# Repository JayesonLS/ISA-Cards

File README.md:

ISA-Cards
=========

ISA card designs for use in Vintage PCs.

ISA Template
============

**Status:** Fit tested and appears correct.

**Description:** A template from which to build ISA cards. The board dimensions
around the edge connector are from an early IBM PC Technical
Reference Manual (5150 or 5160). The rear bracket positioning
has been measured from an original IBM floppy controller taken
from an IBM 5150. This board was an excellent fit when test-fitted
in an early Tandy 1000 (25-1000).

The mounting for the CF adapter has also been comfirmed in the
same Tandy 1000. It too was a excellent fit. 

There may be some variation in fit due to various tolerances. 
The fit does not seem to be particularly important - a wide variation
in fit has been found across various commercial ISA cards.

Tandy PLUS Template
===================

**Status:** Untested.

**Description:** A template from which to design cards and/or back plates
for the Tandy 1000 EX/HX computers. Includes approximate board outlines
as measured from Tandy's memory/DMA board, Tandy's serial board and
Rob Krinecki's 3 in 1 board. Includes various notes about safe areas,
potential places to extend the board dimensions, etc.

CF-Combo-Super-Lite <sup>1, 2</sup>
===================

**Status:** Design built and tested in all configurations. **There is a currently
an error which may cause issues when other devices are performing DMA transfers.
Recommend only the Tandy 1000 configuration of this card which has no DMA present.** 
 
**Description:** An 8 bit ISA card with fully-contained compact flash card and
XT-IDE BIOS. This simplified design uses only 3 ICs for the CF/BIOS functionality.
It makes use of a commonly availalbe, inexpensive compact flash adapter with
integrated mounting bracket.

The board optionally supports the following features:

* An integrated DS1216-E compatible SmartWatch. See 
  https://github.com/JayesonLS/SmartWatchRedux for more information
   about the Dallas SmartWatch.
* 512K of SRAM for the Tandy 1000, 1000A or 1000 HD models only
  (25-1000, 25-1000A, 25-1001). This will bring a stock Tandy
  1000 to 640K. Remove any other memory upgradebefore installing.
  *Do not use the 512K RAM option in any other model of Tandy 1000
  or PC. The memory mapping is only correct for the supported Tandy
  1000 models and will result in memory conflicts in any other system.*

BasicSerial
===========

**Status:** Built and fully tested. The Rear bracket is located too
high and needs to be corrected. No other issues found.

**Description:** Adds a single 9 pin serial port to a vintage PC. Created with early
Tandy 1000's in mind which have no COM ports from the factory.

Decoding is handled by a 74xx688. Alternatively, a JED file is provided
for programming the needed decode functionality into a GAL16V8/ATF16V8.

**Configuration:** Before installing, configure the port selection jumpers
to a COM port not yet present in the system. Details are located on the
board by the port jumpers. Configure the IRQ jumper to an approriate
selection. For no IRQ, remove the IRQ jumper. Suggested IRQ settings are
located on the board by the IRQ jumper.

DualSerial <sup>1</sup>
==========

**Status:** Untested. Vertical positions of serial connectors are only
approximate (waiting on a bracket to arrive for reference).

**Description:** Adds *two* 9 pin serial ports to a vintage PC. Created with early
Tandy 1000's in mind which have no COM ports from the factory.

**Configuration:** Before installing, configure the port selection jumpers
to COM ports not yet present in the system. Details are located on the
board by the port jumpers. Configure the IRQ jumpers to an approriate
selection. For no IRQ, remove the IRQ jumper. Suggested IRQ settings are
located on the board by the IRQ jumpers.

EX-HX Combo <sup>1, 2</sup>
===========

**Status:** Still in design.

**Description:** Multiple upgrades for the Tandy 1000 EX/HX
in a single board. It adds the following:
* Up to 384K of additional base memory to bring the EX/HX up
  to 640K
* Up to 160K of upper memory (UMB)
* Rear accessable CF card slot
* XT-IDE BIOS
* Serial port with 16550 UART 
* DS1316 SmartWatch real time clock

Functionality is very similar to Rob Krinecki's 3 in 1/4 in 1 boards,
with the following differences:
* Can be fitted in either the lower or middle board position on the
  EX/HX.
* Can be used together with Tandy's original DMA/memory board. This
  configuration adds DMA functionality and makes the top board 
  position available for a third upgrade board.
* Support for additional upper memory on the Tandy 1000 EX. The EX
  allows for more upper memory than the HX due to the EX having a
  smaller system ROM than the HX. 
* Base and upper memory configuration, COM port selection, COM IRQ,
  ATA (IDE) port address, etc. are configurable via dip switches.
  Using the default settings, the board is equivalent to the proven
  configuration of Rob Krineki's 3 in 1 board.

Riser
=====

**Status:** Tested and works well. 

**Description:** Raises an 8 bit ISA card up out of a desktop case. Makes it easier
to probe ISA cards during development/testing. Can optionally fuse
the ISA power rails. Low-ohm resistors can be fitted to the power 
rails to assist with current measurement. ISA pins are marked for 
easy identification.

Not intended for permanent installation. 

The bracket is from a Compact Flash to IDE adapter intended for
installation into PCI slots. It must be raised off the board using
standoffs totalling 14.6mm high.

ISAtoTandyPlus
==============

**Status:** Untested.

**Description:** Allows connection of a Tandy 1000 EX/HX Plus board in a standard
ISA slot. Intended for use on an ISA riser board for 
development/testing. 

Not intended for permanent installation.

---------------
<sup>**1**</sup> Construction requires programming of one or
    more GAL16V8/ATF16V8 and/or GAL22V10/ATF22V10 simple programmable
    logic devices. JED file provided. A TL866 or similar programmer
    can program most of these devices.
    
<sup>**2**</sup> Construction requires programming of the required
    BIOS image into the flash ROM. Most common programmers, such as
    the TL866, can be used for this.

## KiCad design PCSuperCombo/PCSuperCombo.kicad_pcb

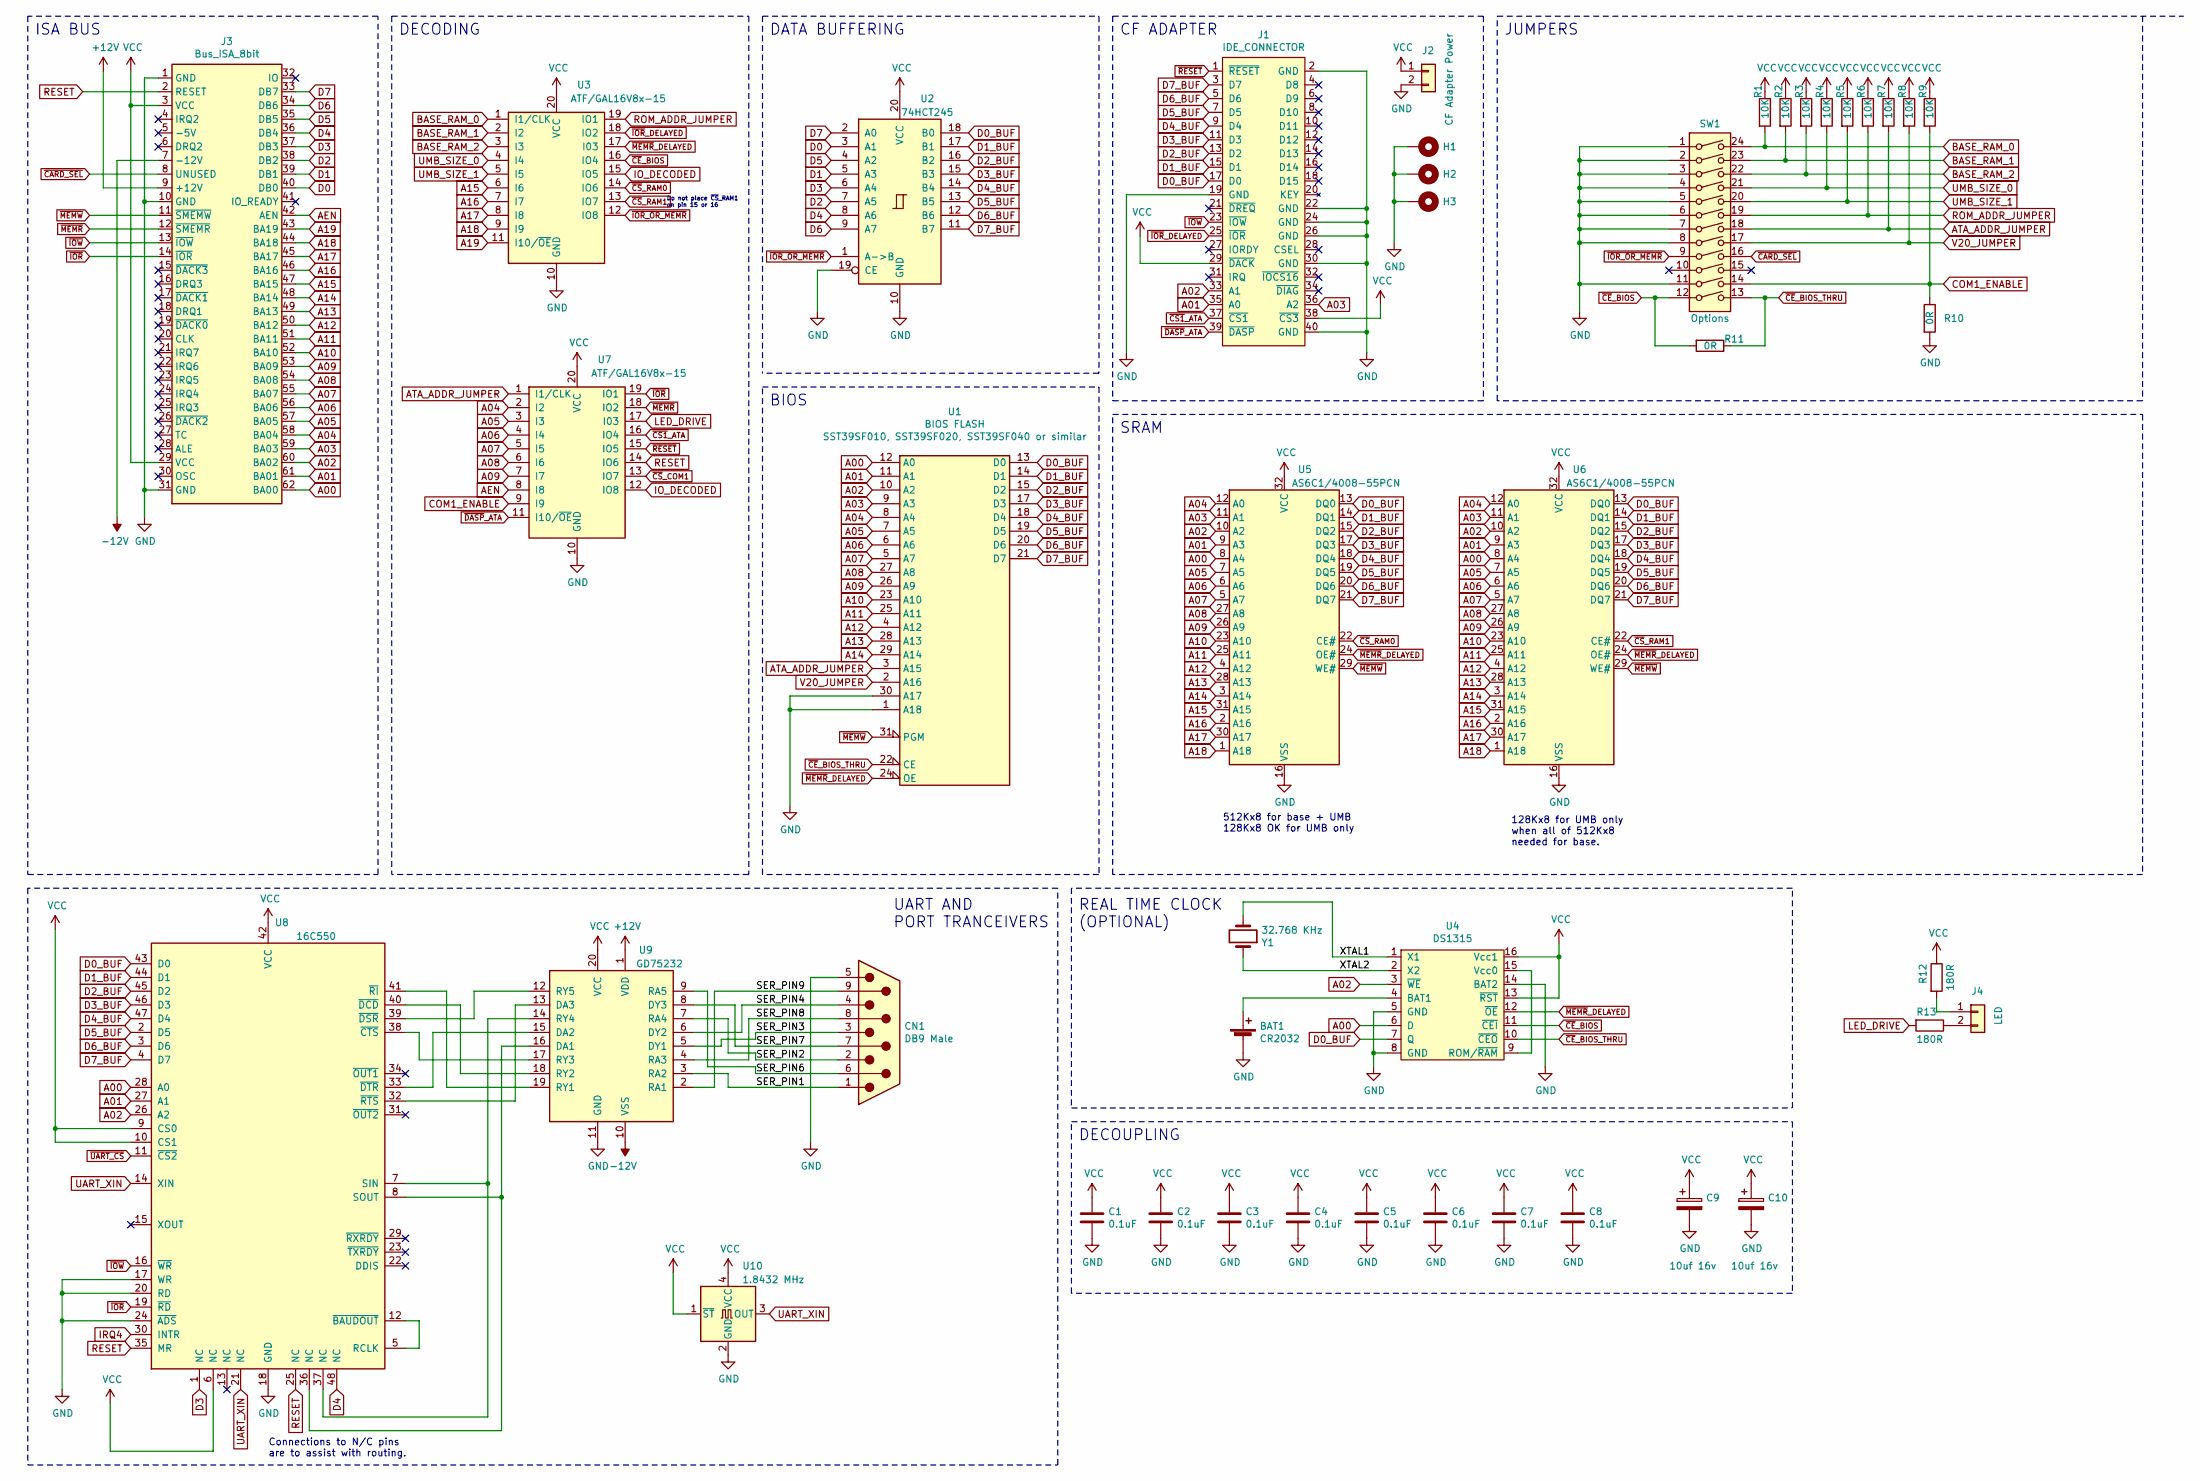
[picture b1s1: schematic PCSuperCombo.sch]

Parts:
BAT1: CR2032; BatteryHolder_Keystone_103_1x20mm
C1, C2, C3, C4, C5, C6, C7, C8: 0.1uF; C_1206_3216Metric; LCSC C24497
C9, C10: 10uf 16v; CP_EIA-3216-18_Kemet-A; LCSC C7171
CN1: DB9 Male; DSUB-9_Male_Horizontal_P2.77x2.84mm_EdgePinOffset7.70mm_Hou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
H1, H2, H3: MountingHole_Pad; MountingHole_3.5mm_Pad
J1: IDE_CONNECTOR; PinSocket_2x20_P2.54mm_Vertical
J2: CF Adapter Power; PinSocket_1x02_P2.54mm_Vertical
J3: Bus_ISA_8bit; BUS_XT
J4: LED; PinHeader_1x02_P2.54mm_Horizontal
R1, R2, R3, R4, R5, R6, R7, R8, R9: 10K; R_1206_3216Metric; LCSC C17902
R10, R11: 0R; R_1206_3216Metric; LCSC C17902
R12, R13: 180R; R_1206_3216Metric; LCSC C17924
SW1: Options; SW_DIP_SPSTx12
U1: BIOS FLASH; DIP-32_W15.24mm_Socket
U2: 74HCT245; DIP-20_W7.62mm_Socket
U3, U7: ATF/GAL16V8x-15; DIP-20_W7.62mm_Socket
U4: DS1315; DIP-16_W7.62mm_Socket
U5, U6: AS6C1/4008-55PCN; DIP-32_W15.24mm_Socket
U8: 16C550; LQFP-48_7x7mm_P0.5mm; Part options C181382, C2692304, C84320, C352984; LCSC C181382
U9: GD75232; SOIC-20W_7.5x12.8mm_P1.27mm; LCSC C6662
U10: 1.8432 MHz; Oscillator_SMD_SeikoEpson_SG8002CA-4Pin_7.0x5.0mm; LCSC C386895
Y1: 32.768 KHz; Crystal_C38-LF_D3.0mm_L8.0mm_Horizontal

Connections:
+12V: J3.9 (+12V), U9.1 (VDD)
-12V: J3.7 (-12V), U9.10 (VSS)
/SER_PIN1: CN1.1, U9.3 (RA2)
/SER_PIN2: CN1.2, U9.7 (RA4)
/SER_PIN3: CN1.3, U9.5 (DY1)
/SER_PIN4: CN1.4, U9.6 (DY2)
/SER_PIN6: CN1.6, U9.9 (RA5)
/SER_PIN7: CN1.7, U9.8 (DY3)
/SER_PIN8: CN1.8, U9.4 (RA3)
/SER_PIN9: CN1.9, U9.2 (RA1)
/XTAL1: U4.1 (X1), Y1.2
/XTAL2: U4.2 (X2), Y1.1
A00: J3.62 (BA00), U1.12 (A0), U4.6 (D), U5.8 (A4), U6.8 (A4), U8.28 (A0)
A01: J1.35 (A0), J3.61 (BA01), U1.11 (A1), U5.9 (A3), U6.9 (A3), U8.27 (A1)
A02: J1.33 (A1), J3.60 (BA02), U1.10 (A2), U4.3 (~WE), U5.10 (A2), U6.10 (A2), U8.26 (A2)
A03: J1.36 (A2), J3.59 (BA03), U1.9 (A3), U5.11 (A1), U6.11 (A1)
A04: J3.58 (BA04), U1.8 (A4), U5.12 (A0), U6.12 (A0), U7.2 (I2)
A05: J3.57 (BA05), U1.7 (A5), U5.7 (A5), U6.7 (A5), U7.3 (I3)
A06: J3.56 (BA06), U1.6 (A6), U5.6 (A6), U6.6 (A6), U7.4 (I4)
A07: J3.55 (BA07), U1.5 (A7), U5.5 (A7), U6.5 (A7), U7.5 (I5)
A08: J3.54 (BA08), U1.27 (A8), U5.27 (A8), U6.27 (A8), U7.6 (I6)
A09: J3.53 (BA09), U1.26 (A9), U5.26 (A9), U6.26 (A9), U7.7 (I7)
A10: J3.52 (BA10), U1.23 (A10), U5.23 (A10), U6.23 (A10)
A11: J3.51 (BA11), U1.25 (A11), U5.25 (A11), U6.25 (A11)
A12: J3.50 (BA12), U1.4 (A12), U5.4 (A12), U6.4 (A12)
A13: J3.49 (BA13), U1.28 (A13), U5.28 (A13), U6.28 (A13)
A14: J3.48 (BA14), U1.29 (A14), U5.3 (A14), U6.3 (A14)
A15: J3.47 (BA15), U3.6 (I6), U5.31 (A15), U6.31 (A15)
A16: J3.46 (BA16), U3.7 (I7), U5.2 (A16), U6.2 (A16)
A17: J3.45 (BA17), U3.8 (I8), U5.30 (A17), U6.30 (A17)
A18: J3.44 (BA18), U3.9 (I9), U5.1 (A18), U6.1 (A18)
A19: J3.43 (BA19), U3.11 (I10/~OE~)
AEN: J3.42 (AEN), U7.8 (I8)
ATA_ADDR_JUMPER: R7.2, SW1.18, U1.3 (A15), U7.1 (I1/CLK)
BASE_RAM_0: R1.2, SW1.24, U3.1 (I1/CLK)
BASE_RAM_1: R2.2, SW1.23, U3.2 (I2)
BASE_RAM_2: R3.2, SW1.22, U3.3 (I3)
COM1_ENABLE: R9.2, R10.1, SW1.14, U7.9 (I9)
D0: J3.40 (DB0), U2.3 (A1)
D0_BUF: J1.17 (D0), U1.13 (D0), U2.18 (B0), U4.7 (Q), U5.13 (DQ0), U6.13 (DQ0), U8.43 (D0)
D1: J3.39 (DB1), U2.5 (A3)
D1_BUF: J1.15 (D1), U1.14 (D1), U2.17 (B1), U5.14 (DQ1), U6.14 (DQ1), U8.44 (D1)
D2: J3.38 (DB2), U2.7 (A5)
D2_BUF: J1.13 (D2), U1.15 (D2), U2.16 (B2), U5.15 (DQ2), U6.15 (DQ2), U8.45 (D2)
D3: J3.37 (DB3), U2.6 (A4), U8.1 (NC)
D3_BUF: J1.11 (D3), U1.17 (D3), U2.15 (B3), U5.17 (DQ3), U6.17 (DQ3), U8.46 (D3)
D4: J3.36 (DB4), U2.8 (A6), U8.48 (NC)
D4_BUF: J1.9 (D4), U1.18 (D4), U2.14 (B4), U5.18 (DQ4), U6.18 (DQ4), U8.47 (D4)
D5: J3.35 (DB5), U2.4 (A2)
D5_BUF: J1.7 (D5), U1.19 (D5), U2.13 (B5), U5.19 (DQ5), U6.19 (DQ5), U8.2 (D5)
D6: J3.34 (DB6), U2.9 (A7)
D6_BUF: J1.5 (D6), U1.20 (D6), U2.12 (B6), U5.20 (DQ6), U6.20 (DQ6), U8.3 (D6)
D7: J3.33 (DB7), U2.2 (A0)
D7_BUF: J1.3 (D7), U1.21 (D7), U2.11 (B7), U5.21 (DQ7), U6.21 (DQ7), U8.4 (D7)
GND: BAT1.2 (-), C1.2, C2.2, C3.2, C4.2, C5.2, C6.2, C7.2, C8.2, C9.2, C10.2, CN1.5, H1.1, H2.1, H3.1, J1.2 (GND), J1.19 (GND), J1.22 (GND), J1.24 (GND), J1.26 (GND), J1.30 (GND), J1.40 (GND), J2.2, J3.1 (GND), J3.10 (GND), J3.31 (GND), R10.2, SW1.1, SW1.2, SW1.3, SW1.4, SW1.5, SW1.6, SW1.7, SW1.8, SW1.11, U1.1 (A18), U1.16 (GND), U1.30 (A17), U2.10 (GND), U2.19 (CE), U3.10 (GND), U4.5 (GND), U4.8 (GND), U4.14 (BAT2), U5.16 (VSS), U6.16 (VSS), U7.10 (GND), U8.17 (WR), U8.18 (GND), U8.20 (RD), U8.24 (~ADS~), U9.11 (GND), U10.2 (GND)
IO_DECODED: U3.15 (IO5), U7.12 (IO8)
IRQ4: U8.30 (INTR)
LED_DRIVE: R13.2, U7.17 (I03)
unnamed: BAT1.1 (+), U4.4 (BAT1)
unnamed: J4.1, R12.2
unnamed: J4.2, R13.1
unnamed: U4.9 (ROM/~RAM), U4.15 (Vcc0)
unnamed: U8.5 (RCLK), U8.12 (~BAUDOUT~)
unnamed: U8.32 (~RTS~), U9.13 (DA3)
unnamed: U8.33 (~DTR~), U9.15 (DA2)
unnamed: U8.8 (SOUT), U8.36 (NC), U9.16 (DA1)
unnamed: U8.7 (SIN), U8.37 (NC), U9.14 (RY4)
unnamed: U8.38 (~CTS~), U9.17 (RY3)
unnamed: U8.39 (~DSR~), U9.12 (RY5)
unnamed: U8.40 (~DCD~), U9.18 (RY2)
unnamed: U8.41 (~RI~), U9.19 (RY1)
RESET: J3.2 (RESET), U7.14 (IO6), U8.25 (NC), U8.35 (MR)
ROM_ADDR_JUMPER: R6.2, SW1.19, U3.19 (IO1)
UART_XIN: U8.14 (XIN), U8.21 (NC), U10.3 (OUT)
UMB_SIZE_0: R4.2, SW1.21, U3.4 (I4)
UMB_SIZE_1: R5.2, SW1.20, U3.5 (I5)
V20_JUMPER: R8.2, SW1.17, U1.2 (A16)
VCC: C1.1, C2.1, C3.1, C4.1, C5.1, C6.1, C7.1, C8.1, C9.1, C10.1, J1.29 (~DACK), J1.38 (~CS3), J2.1, J3.3 (VCC), J3.29 (VCC), R1.1, R2.1, R3.1, R4.1, R5.1, R6.1, R7.1, R8.1, R9.1, R12.1, U1.32 (VCC), U2.20 (VCC), U3.20 (VCC), U4.13 (~RST), U4.16 (Vcc1), U5.32 (VCC), U6.32 (VCC), U7.20 (VCC), U8.6 (NC), U8.9 (CS0), U8.10 (CS1), U8.42 (VCC), U9.20 (VCC), U10.1 (~ST), U10.4 (VCC)
~CARD_SEL: J3.8 (UNUSED), SW1.16
~CE~_BIOS: R11.2, SW1.12, U3.16 (IO4), U4.11 (~CEI)
~CE~_BIOS_THRU: R11.1, SW1.13, U1.22 (CE), U4.10 (~CEO)
~CS1~_ATA: J1.37 (~CS1), U7.16 (IO4)
~CS~_COM1: U7.13 (IO7)
~CS~_RAM0: U3.14 (IO6), U5.22 (CE#)
~CS~_RAM1: U3.13 (IO7), U6.22 (CE#)
~DASP~_ATA: J1.39 (~DASP), U7.11 (I10/~OE~)
~IOR: J3.14 (~IOR), U7.19 (IO1), U8.19 (~RD~)
~IOR_OR_MEMR: SW1.9, U2.1 (A->B), U3.12 (IO8)
~IOR~_DELAYED: J1.25 (~IOR), U3.18 (IO2)
~IOW: J1.23 (~IOW), J3.13 (~IOW), U8.16 (~WR~)
~MEMR: J3.12 (~SMEMR), U7.18 (IO2)
~MEMR~_DELAYED: U1.24 (OE), U3.17 (I03), U4.12 (~OE), U5.24 (OE#), U6.24 (OE#)
~MEMW: J3.11 (~SMEMW), U1.31 (PGM), U5.29 (WE#), U6.29 (WE#)
~RESET: J1.1 (~RESET), U7.15 (IO5)
~UART_CS: U8.11 (~CS2~)

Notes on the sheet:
ISA BUS
DECOUPLING
BIOS
JUMPERS
REAL TIME CLOCK (OPTIONAL)
SRAM
512Kx8 for base + UMB 128Kx8 OK for UMB only
128Kx8 for UMB only when all of 512Kx8 needed for base.
CF ADAPTER
DECODING
DATA BUFFERING
Do not place ~CS~_RAM1 on pin 15 or 16
UART AND PORT TRANCEIVERS
Connections to N/C pins are to assist with routing.

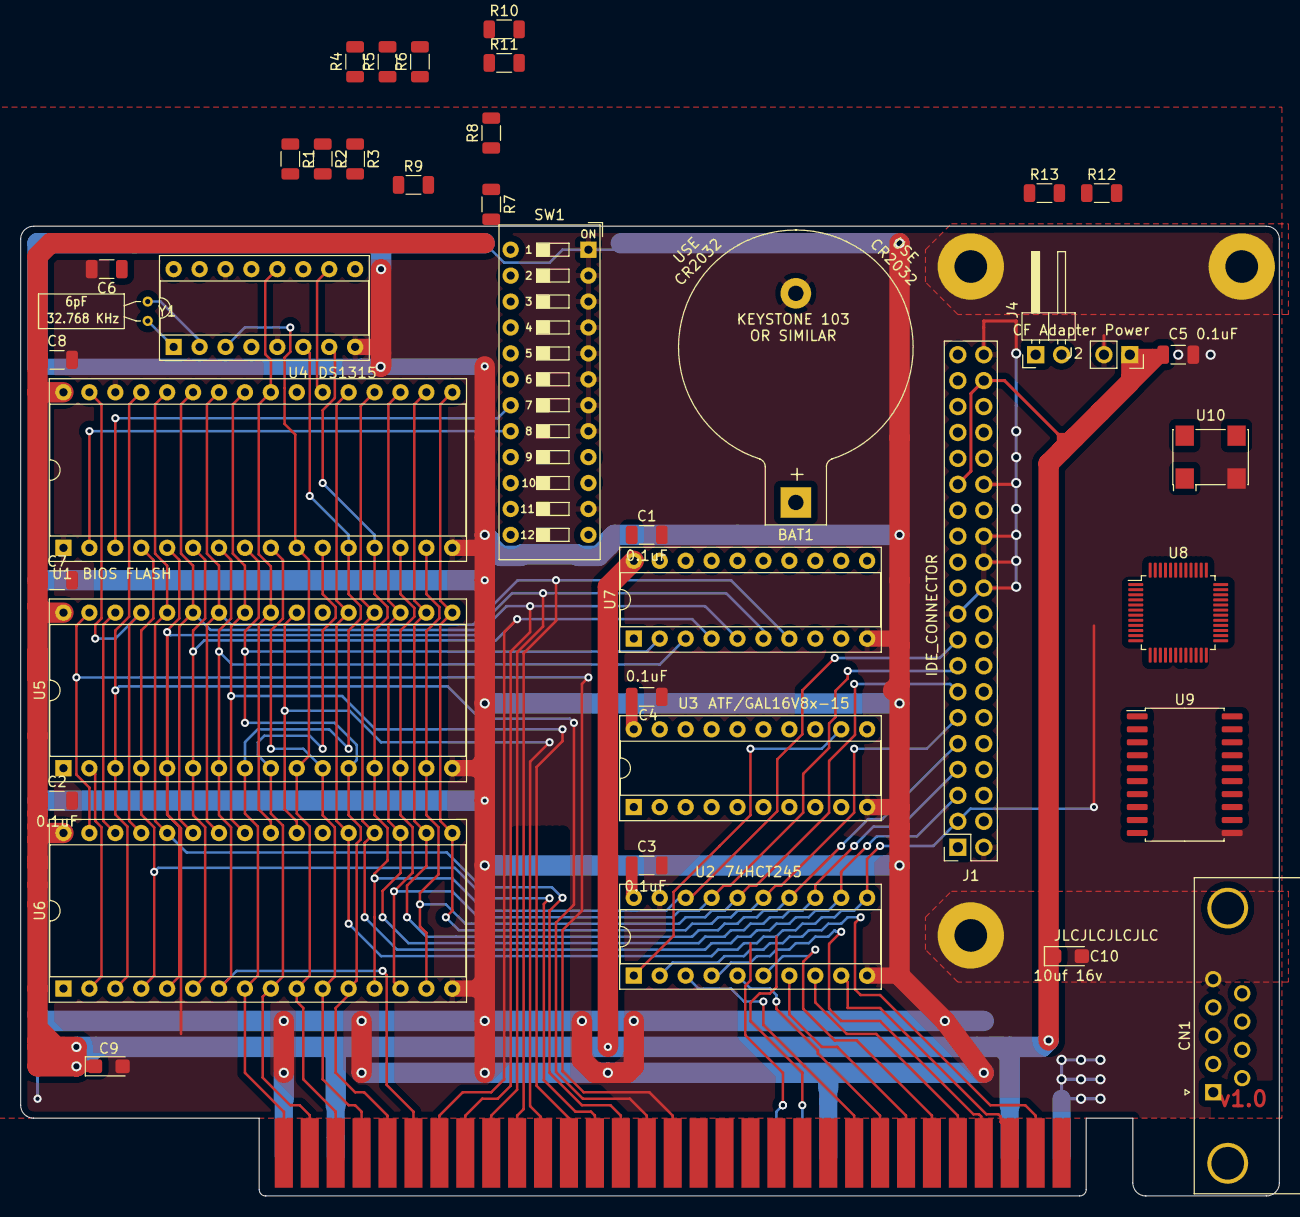
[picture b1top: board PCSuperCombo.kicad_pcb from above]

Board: 2 copper layers, 123.3 x 95.0 mm, 44 parts (0 on the bottom side), 92 nets.

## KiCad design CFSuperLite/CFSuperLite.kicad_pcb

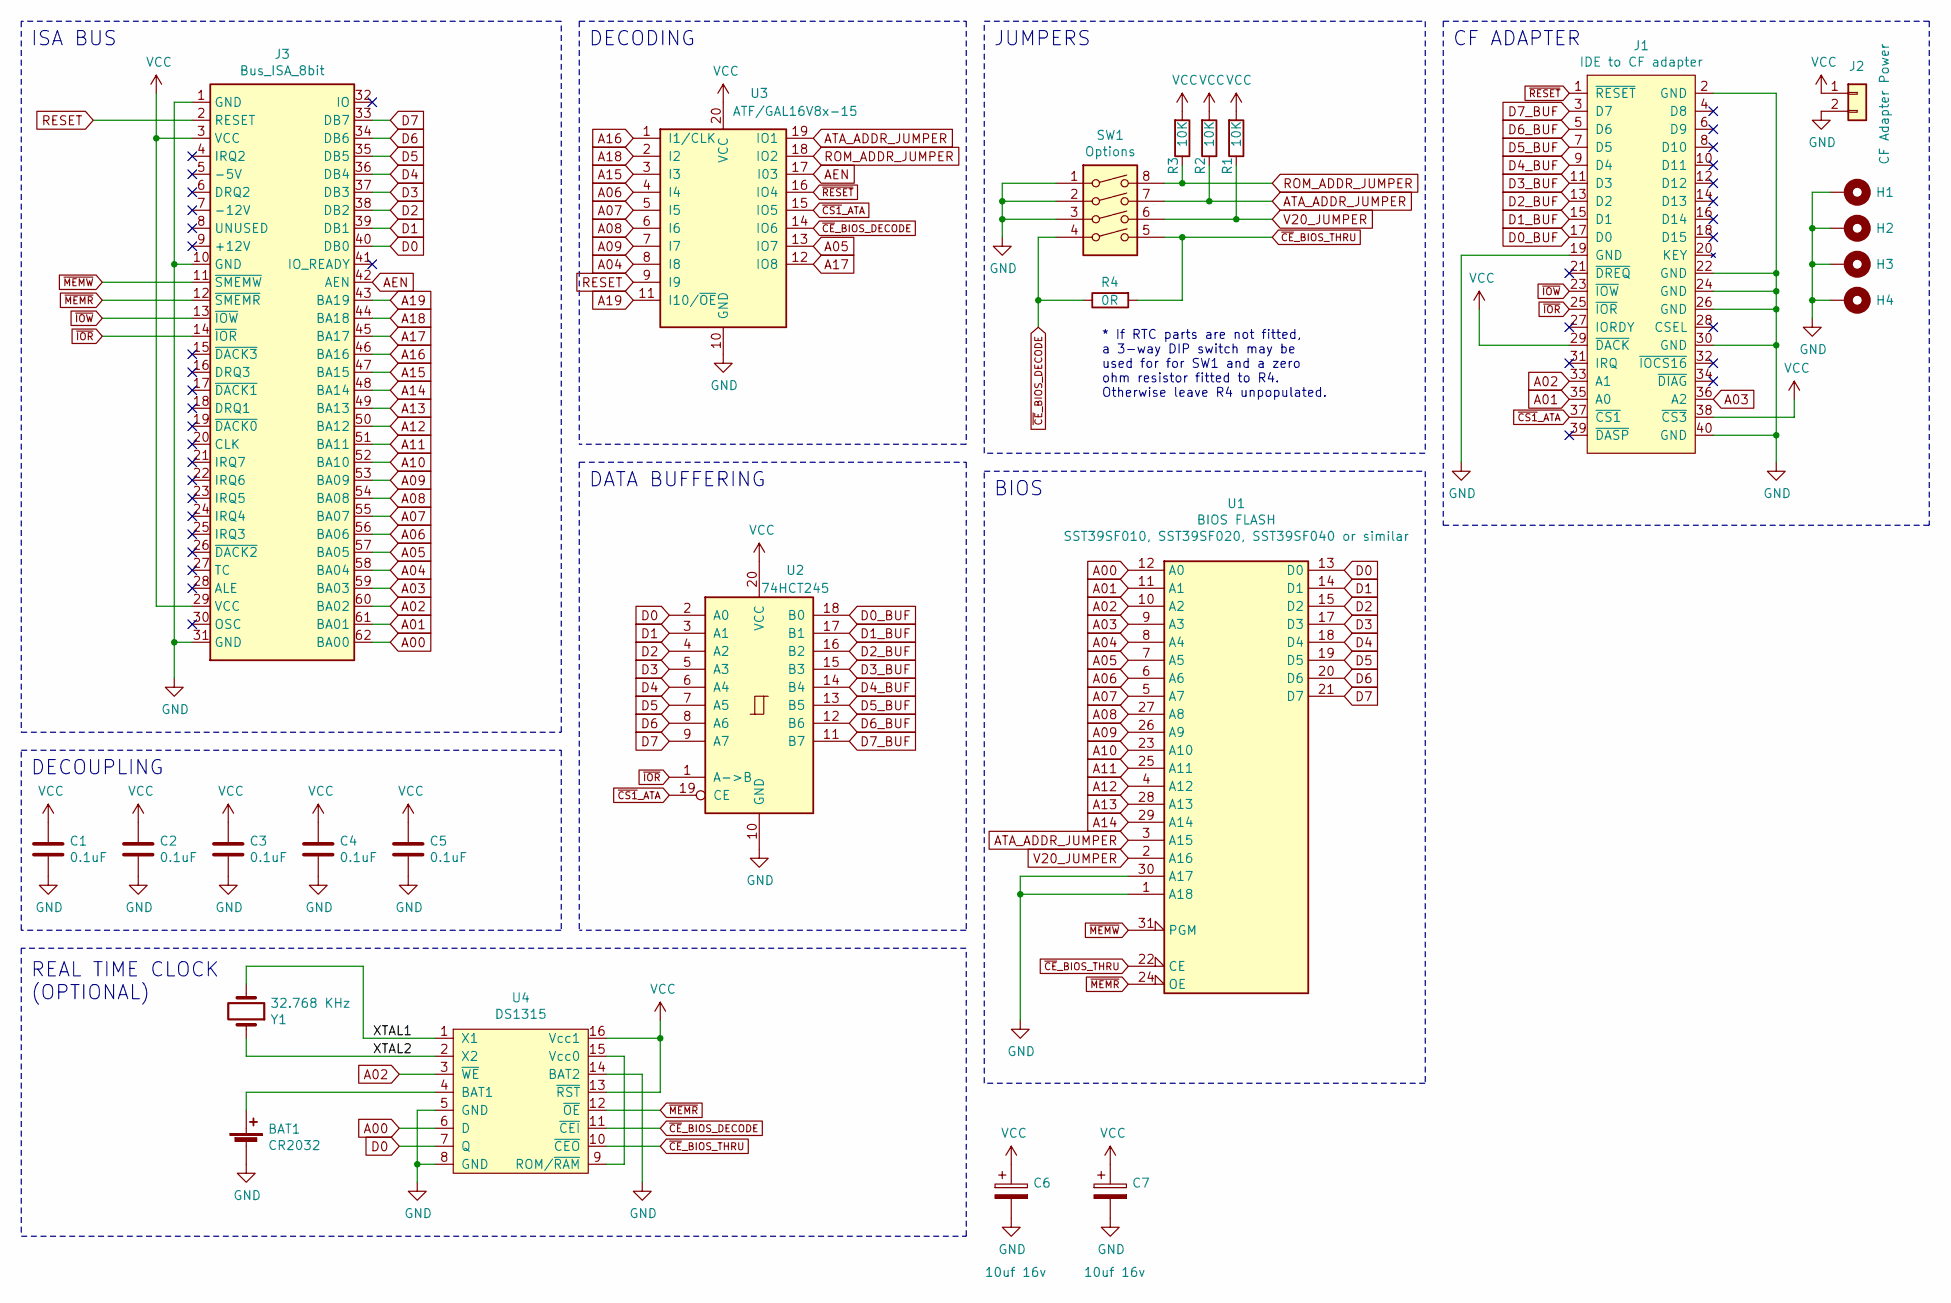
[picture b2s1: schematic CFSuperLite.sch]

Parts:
BAT1: CR2032; BatteryHolder_Keystone_103_1x20mm; Part options C964748, C964751, C964750; LCSC C964748
C1, C2, C3, C4, C5: 0.1uF; C_1206_3216Metric; LCSC C24497
C6, C7: 10uf 16v; CP_EIA-3216-18_Kemet-A; LCSC C7171
H1, H2, H3, H4: MountingHole_Pad; MountingHole_3.5mm_Pad
J1: IDE to CF adapter; PinSocket_2x20_P2.54mm_Vertical; LCSC C35165
J2: CF Adapter Power; PinSocket_1x02_P2.54mm_Vertical; Part options C225499, C49661; LCSC C225499
J3: Bus_ISA_8bit; BUS_XT
R1, R2, R3: 10K; R_1206_3216Metric; LCSC C17902
R4: 0R; R_1206_3216Metric; LCSC C17888
SW1: Options; SW_DIP_SPSTx04_Slide_9.78x12.34mm_W7.62mm_P2.54mm; Part options C15781, C99418, C319060, C47207; LCSC C15781
U1: BIOS FLASH; DIP-32_W15.24mm_Socket; Part options C72122, C146583, C2331; LCSC C146583
U2: 74HCT245; DIP-20_W7.62mm_Socket; Part options C72118, C132507, C2328; LCSC C72118
U3: ATF/GAL16V8x-15; DIP-20_W7.62mm_Socket; Part options C72118, C132507, C2328; LCSC C72118
U4: DS1315; DIP-16_W7.62mm_Socket; Part options C72115, C146580, C2326; LCSC C72115
Y1: 32.768 KHz; Crystal_C38-LF_D3.0mm_L8.0mm_Horizontal; LCSC C127496

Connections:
/XTAL1: U4.1 (X1), Y1.2
/XTAL2: U4.2 (X2), Y1.1
A00: J3.62 (BA00), U1.12 (A0), U4.6 (D)
A01: J1.35 (A0), J3.61 (BA01), U1.11 (A1)
A02: J1.33 (A1), J3.60 (BA02), U1.10 (A2), U4.3 (~WE)
A03: J1.36 (A2), J3.59 (BA03), U1.9 (A3)
A04: J3.58 (BA04), U1.8 (A4), U3.8 (I8)
A05: J3.57 (BA05), U1.7 (A5), U3.13 (IO7)
A06: J3.56 (BA06), U1.6 (A6), U3.4 (I4)
A07: J3.55 (BA07), U1.5 (A7), U3.5 (I5)
A08: J3.54 (BA08), U1.27 (A8), U3.6 (I6)
A09: J3.53 (BA09), U1.26 (A9), U3.7 (I7)
A10: J3.52 (BA10), U1.23 (A10)
A11: J3.51 (BA11), U1.25 (A11)
A12: J3.50 (BA12), U1.4 (A12)
A13: J3.49 (BA13), U1.28 (A13)
A14: J3.48 (BA14), U1.29 (A14)
A15: J3.47 (BA15), U3.3 (I3)
A16: J3.46 (BA16), U3.1 (I1/CLK)
A17: J3.45 (BA17), U3.12 (IO8)
A18: J3.44 (BA18), U3.2 (I2)
A19: J3.43 (BA19), U3.11 (I10/~OE~)
AEN: J3.42 (AEN), U3.17 (I03)
ATA_ADDR_JUMPER: R2.1, SW1.7, U1.3 (A15), U3.19 (IO1)
D0: J3.40 (DB0), U1.13 (D0), U2.2 (A0), U4.7 (Q)
D0_BUF: J1.17 (D0), U2.18 (B0)
D1: J3.39 (DB1), U1.14 (D1), U2.3 (A1)
D1_BUF: J1.15 (D1), U2.17 (B1)
D2: J3.38 (DB2), U1.15 (D2), U2.4 (A2)
D2_BUF: J1.13 (D2), U2.16 (B2)
D3: J3.37 (DB3), U1.17 (D3), U2.5 (A3)
D3_BUF: J1.11 (D3), U2.15 (B3)
D4: J3.36 (DB4), U1.18 (D4), U2.6 (A4)
D4_BUF: J1.9 (D4), U2.14 (B4)
D5: J3.35 (DB5), U1.19 (D5), U2.7 (A5)
D5_BUF: J1.7 (D5), U2.13 (B5)
D6: J3.34 (DB6), U1.20 (D6), U2.8 (A6)
D6_BUF: J1.5 (D6), U2.12 (B6)
D7: J3.33 (DB7), U1.21 (D7), U2.9 (A7)
D7_BUF: J1.3 (D7), U2.11 (B7)
GND: BAT1.2 (-), C1.2, C2.2, C3.2, C4.2, C5.2, C6.2, C7.2, H1.1, H2.1, H3.1, H4.1, J1.2 (GND), J1.19 (GND), J1.22 (GND), J1.24 (GND), J1.26 (GND), J1.30 (GND), J1.40 (GND), J2.2, J3.1 (GND), J3.10 (GND), J3.31 (GND), SW1.1, SW1.2, SW1.3, U1.1 (A18), U1.16 (GND), U1.30 (A17), U2.10 (GND), U3.10 (GND), U4.5 (GND), U4.8 (GND), U4.14 (BAT2)
unnamed: BAT1.1 (+), U4.4 (BAT1)
unnamed: U4.9 (ROM/~RAM), U4.15 (Vcc0)
RESET: J3.2 (RESET), U3.9 (I9)
ROM_ADDR_JUMPER: R1.1, SW1.8, U3.18 (IO2)
V20_JUMPER: R3.1, SW1.6, U1.2 (A16)
VCC: C1.1, C2.1, C3.1, C4.1, C5.1, C6.1, C7.1, J1.29 (~DACK), J1.38 (~CS3), J2.1, J3.3 (VCC), J3.29 (VCC), R1.2, R2.2, R3.2, U1.32 (VCC), U2.20 (VCC), U3.20 (VCC), U4.13 (~RST), U4.16 (Vcc1)
~CE~_BIOS_DECODE: R4.1, SW1.4, U3.14 (IO6), U4.11 (~CEI)
~CE~_BIOS_THRU: R4.2, SW1.5, U1.22 (CE), U4.10 (~CEO)
~CS1~_ATA: J1.37 (~CS1), U2.19 (CE), U3.15 (IO5)
~IOR: J1.25 (~IOR), J3.14 (~IOR), U2.1 (A->B)
~IOW: J1.23 (~IOW), J3.13 (~IOW)
~MEMR: J3.12 (~SMEMR), U1.24 (OE), U4.12 (~OE)
~MEMW: J3.11 (~SMEMW), U1.31 (PGM)
~RESET: J1.1 (~RESET), U3.16 (IO4)

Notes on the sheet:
ISA BUS
DECOUPLING
DATA BUFFERING
DECODING
BIOS
CF ADAPTER
JUMPERS
REAL TIME CLOCK (OPTIONAL)
* If RTC parts are not fitted, a 3-way DIP switch may be used for for SW1 and a zero ohm resistor fitted to R4. Otherwise leave R4 unpopulated.

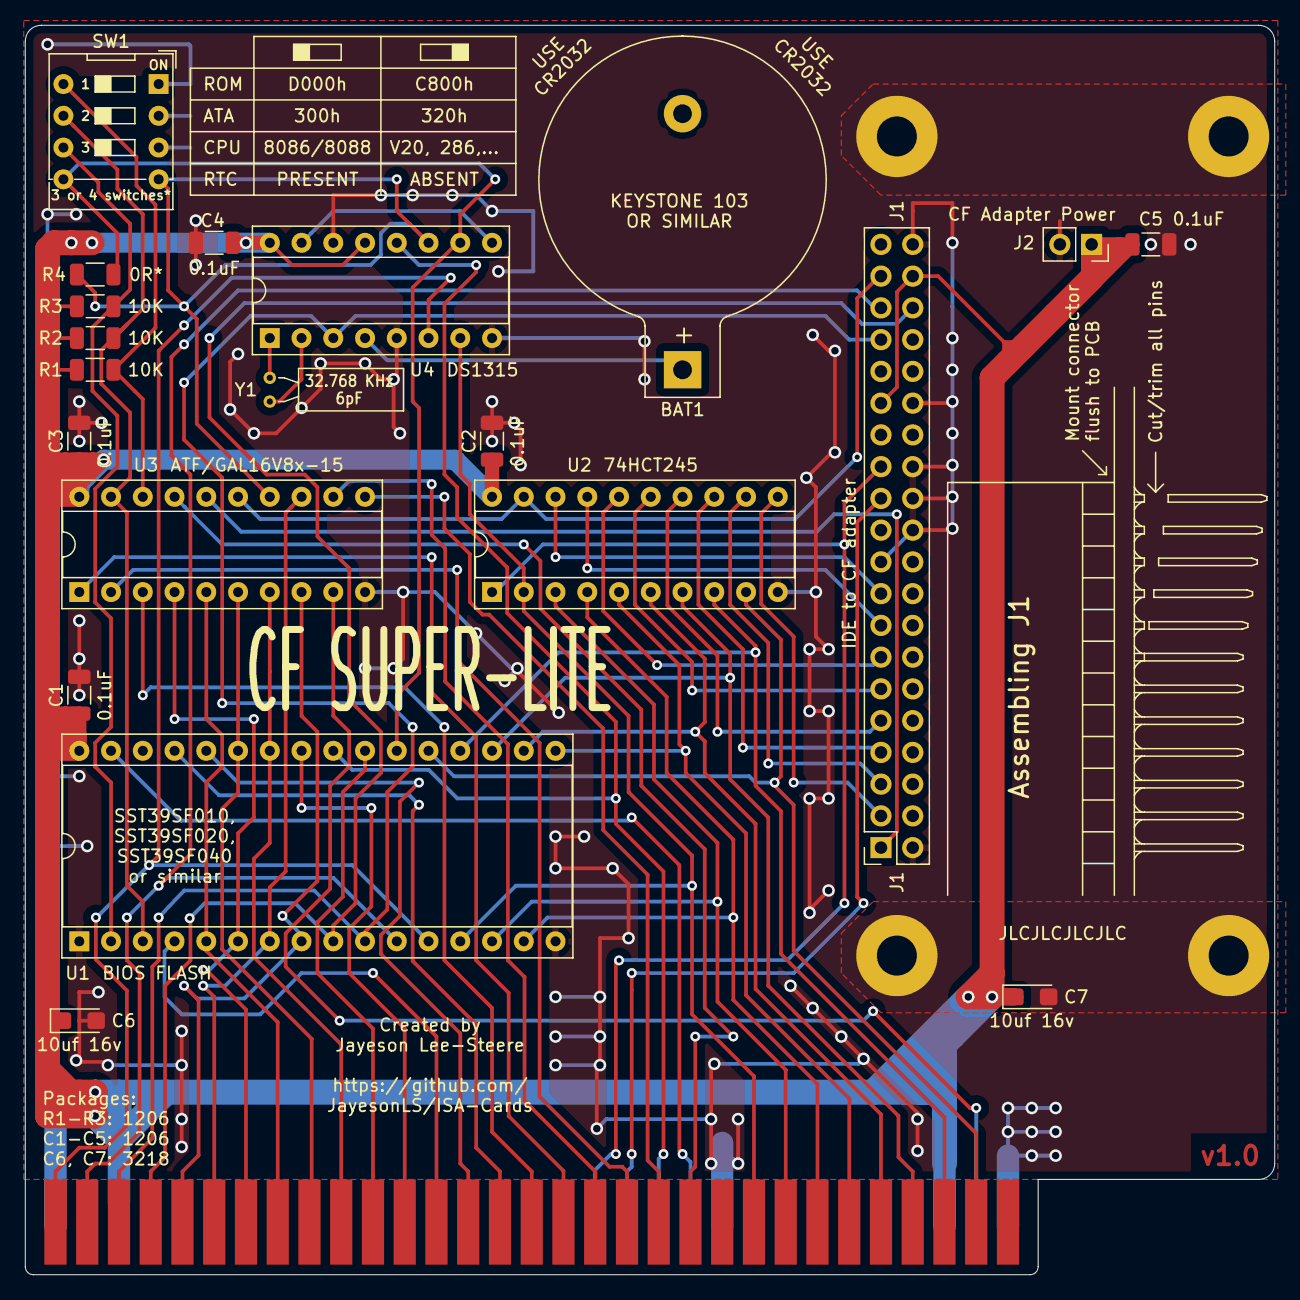
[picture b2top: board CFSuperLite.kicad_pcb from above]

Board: 2 copper layers, 99.9 x 99.9 mm, 25 parts (0 on the bottom side), 55 nets.

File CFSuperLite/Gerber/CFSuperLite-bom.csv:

Comment,Designator,Footprint,LCSC
CR2032,BAT1,Battery:BatteryHolder_Keystone_103_1x20mm,C964748
0.1uF,"C1,C2,C3,C4,C5",Capacitor_SMD:C_1206_3216Metric, C24497
22-44uF 16-25v,C6,Capacitor_Tantalum_SMD:CP_EIA-3528-15_AVX-H,C10785
IDE to CF adapter (mount flush and trim pins after soldering),J1,Connector_PinSocket_2.54mm:PinSocket_2x20_P2.54mm_Vertical,C35165
CF Adapter Power,J2,Connector_PinSocket_2.54mm:PinSocket_1x02_P2.54mm_Vertical,C225499
10K,"R1,R2,R3",Resistor_SMD:R_1206_3216Metric,C17902
Options,SW1,Button_Switch_THT:SW_DIP_SPSTx04_Slide_9.78x12.34mm_W7.62mm_P2.54mm,C15781
BIOS FLASH,U1,Package_DIP:DIP-32_W15.24mm_Socket,C146583
DIP-20 Socket,"U2,U3",Package_DIP:DIP-20_W7.62mm_Socket,C72118
DS1315,U4,Package_DIP:DIP-16_W7.62mm_Socket,C72115
32.768 KHz,Y1,Crystal:Crystal_C38-LF_D3.0mm_L8.0mm_Horizontal,C127496

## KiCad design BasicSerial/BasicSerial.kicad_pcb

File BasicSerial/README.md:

Basic Serial
============

A simple ISA card adding one serial (COM) port to a vintage PC. 
Created with early Tandy 1000's in mind which have no COM ports from the factory.

Configuration
-------------

Before installing, configure the port selection jumpers to a COM port not yet present 
in the system. Details are located on the board by the port jumpers.

Configure the IRQ jumper to an approriate selection. For no IRQ, remove the IRQ jumper.
Suggested IRQ settings are located on the board by the IRQ jumper.

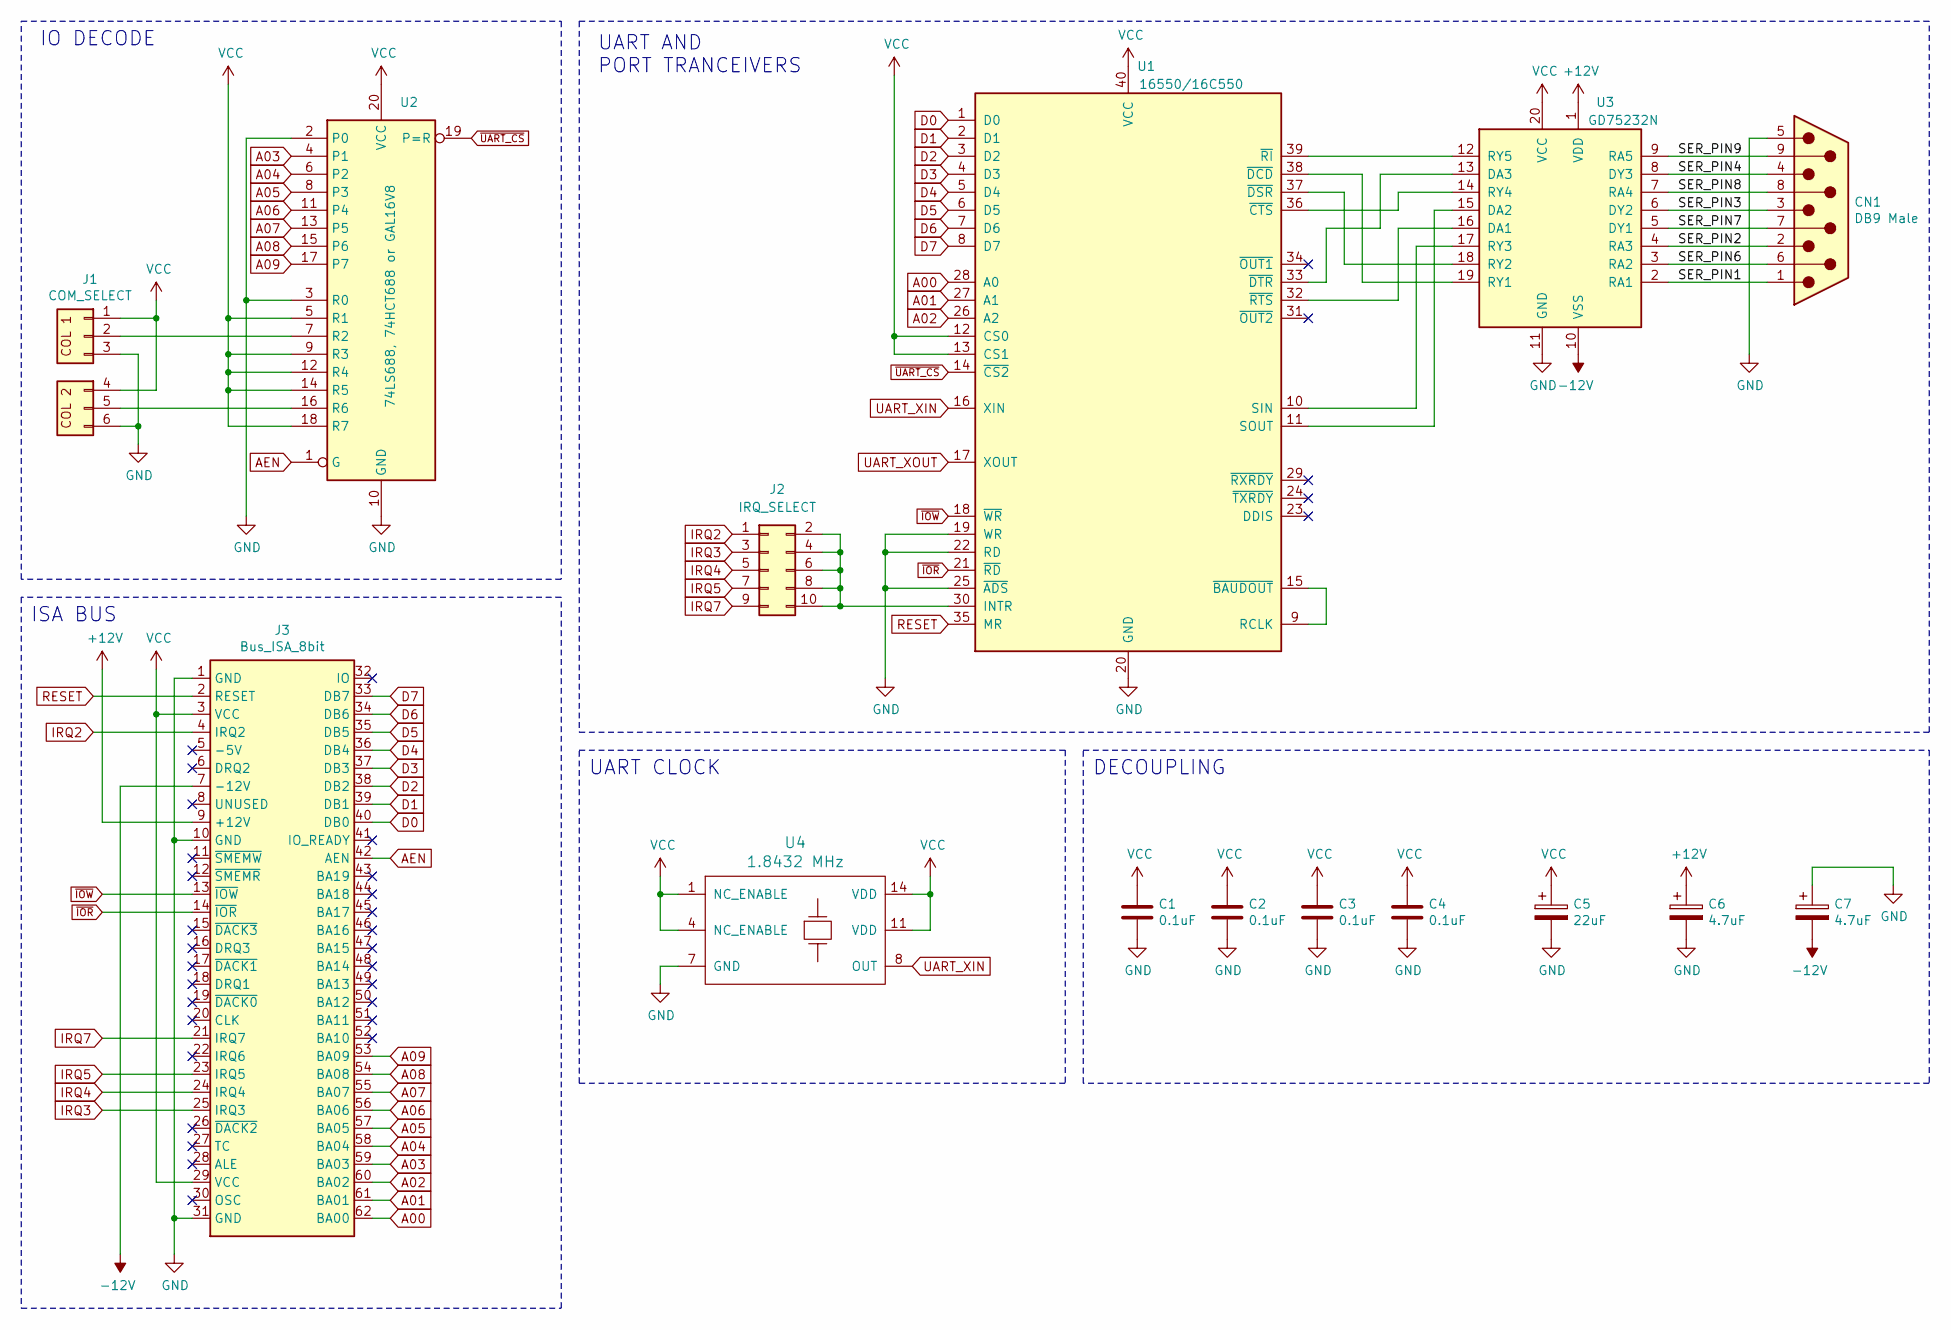
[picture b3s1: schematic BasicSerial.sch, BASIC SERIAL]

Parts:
C1, C2, C3, C4: 0.1uF; C_Disc_D5.1mm_W3.2mm_P5.00mm
C5: 22uF; CP_Radial_D7.5mm_P2.50mm
C6, C7: 4.7uF; CP_Radial_D7.5mm_P2.50mm
CN1: DB9 Male; DB_9M
J1: COM_SELECT; PinHeader_3x02_P2.54mm_Vertical
J2: IRQ_SELECT; PinHeader_2x05_P2.54mm_Vertical
J3: Bus_ISA_8bit; BUS_XT
U1: 16550/16C550; DIP-40_W15.24mm_Socket
U2: 74LS688, 74HCT688 or GAL16V8; DIP-20_W7.62mm_Socket
U3: GD75232N; DIP-20_W7.62mm_Socket
U4: 1.8432 MHz; Crystal_DIP8_DIP14

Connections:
+12V: C6.1, J3.9 (+12V), U3.1 (VDD)
-12V: C7.2, J3.7 (-12V), U3.10 (VSS)
/SER_PIN1: CN1.1, U3.2 (RA1)
/SER_PIN2: CN1.2, U3.4 (RA3)
/SER_PIN3: CN1.3, U3.6 (DY2)
/SER_PIN4: CN1.4, U3.8 (DY3)
/SER_PIN6: CN1.6, U3.3 (RA2)
/SER_PIN7: CN1.7, U3.5 (DY1)
/SER_PIN8: CN1.8, U3.7 (RA4)
/SER_PIN9: CN1.9, U3.9 (RA5)
A00: J3.62 (BA00), U1.28 (A0)
A01: J3.61 (BA01), U1.27 (A1)
A02: J3.60 (BA02), U1.26 (A2)
A03: J3.59 (BA03), U2.4 (P1)
A04: J3.58 (BA04), U2.6 (P2)
A05: J3.57 (BA05), U2.8 (P3)
A06: J3.56 (BA06), U2.11 (P4)
A07: J3.55 (BA07), U2.13 (P5)
A08: J3.54 (BA08), U2.15 (P6)
A09: J3.53 (BA09), U2.17 (P7)
AEN: J3.42 (AEN), U2.1 (G)
D0: J3.40 (DB0), U1.1 (D0)
D1: J3.39 (DB1), U1.2 (D1)
D2: J3.38 (DB2), U1.3 (D2)
D3: J3.37 (DB3), U1.4 (D3)
D4: J3.36 (DB4), U1.5 (D4)
D5: J3.35 (DB5), U1.6 (D5)
D6: J3.34 (DB6), U1.7 (D6)
D7: J3.33 (DB7), U1.8 (D7)
GND: C1.2, C2.2, C3.2, C4.2, C5.2, C6.2, C7.1, CN1.5, J1.3 (Pin_4), J1.6, J3.1 (GND), J3.10 (GND), J3.31 (GND), U1.19 (WR), U1.20 (GND), U1.22 (RD), U1.25 (~ADS~), U2.2 (P0), U2.3 (R0), U2.10 (GND), U3.11 (GND), U4.7 (GND)
IRQ2: J2.1, J3.4 (IRQ2)
IRQ3: J2.3, J3.25 (IRQ3)
IRQ4: J2.5, J3.24 (IRQ4)
IRQ5: J2.7, J3.23 (IRQ5)
IRQ7: J2.9, J3.21 (IRQ7)
unnamed: J1.2, U2.7 (R2)
unnamed: J1.5, U2.16 (R6)
unnamed: J2.2, J2.4, J2.6, J2.8, J2.10, U1.30 (INTR)
unnamed: U1.10 (SIN), U3.17 (RY3)
unnamed: U1.11 (SOUT), U3.15 (DA2)
unnamed: U1.9 (RCLK), U1.15 (~BAUDOUT~)
unnamed: U1.32 (~RTS~), U3.16 (DA1)
unnamed: U1.33 (~DTR~), U3.13 (DA3)
unnamed: U1.36 (~CTS~), U3.14 (RY4)
unnamed: U1.37 (~DSR~), U3.18 (RY2)
unnamed: U1.38 (~DCD~), U3.19 (RY1)
unnamed: U1.39 (~RI~), U3.12 (RY5)
RESET: J3.2 (RESET), U1.35 (MR)
UART_XIN: U1.16 (XIN), U4.8 (OUT)
UART_XOUT: U1.17 (XOUT)
VCC: C1.1, C2.1, C3.1, C4.1, C5.1, J1.1, J1.4, J3.3 (VCC), J3.29 (VCC), U1.12 (CS0), U1.13 (CS1), U1.40 (VCC), U2.5 (R1), U2.9 (R3), U2.12 (R4), U2.14 (R5), U2.18 (R7), U2.20 (VCC), U3.20 (VCC), U4.1 (NC_ENABLE), U4.4 (NC_ENABLE), U4.11 (VDD), U4.14 (VDD)
~IOR: J3.14 (~IOR), U1.21 (~RD~)
~IOW: J3.13 (~IOW), U1.18 (~WR~)
~UART_CS: U1.14 (~CS2~), U2.19 (P=R)

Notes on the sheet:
ISA BUS
IO DECODE
UART AND PORT TRANCEIVERS
UART CLOCK
DECOUPLING

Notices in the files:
BasicSerial/BasicSerial.sch:
Copyright (C) 2021 Titanium Studios Pty Ltd
